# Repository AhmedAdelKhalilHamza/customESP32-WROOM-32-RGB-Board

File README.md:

# custom ESP32 board
custom ESP32 board by Eng/ Ahmed Adel

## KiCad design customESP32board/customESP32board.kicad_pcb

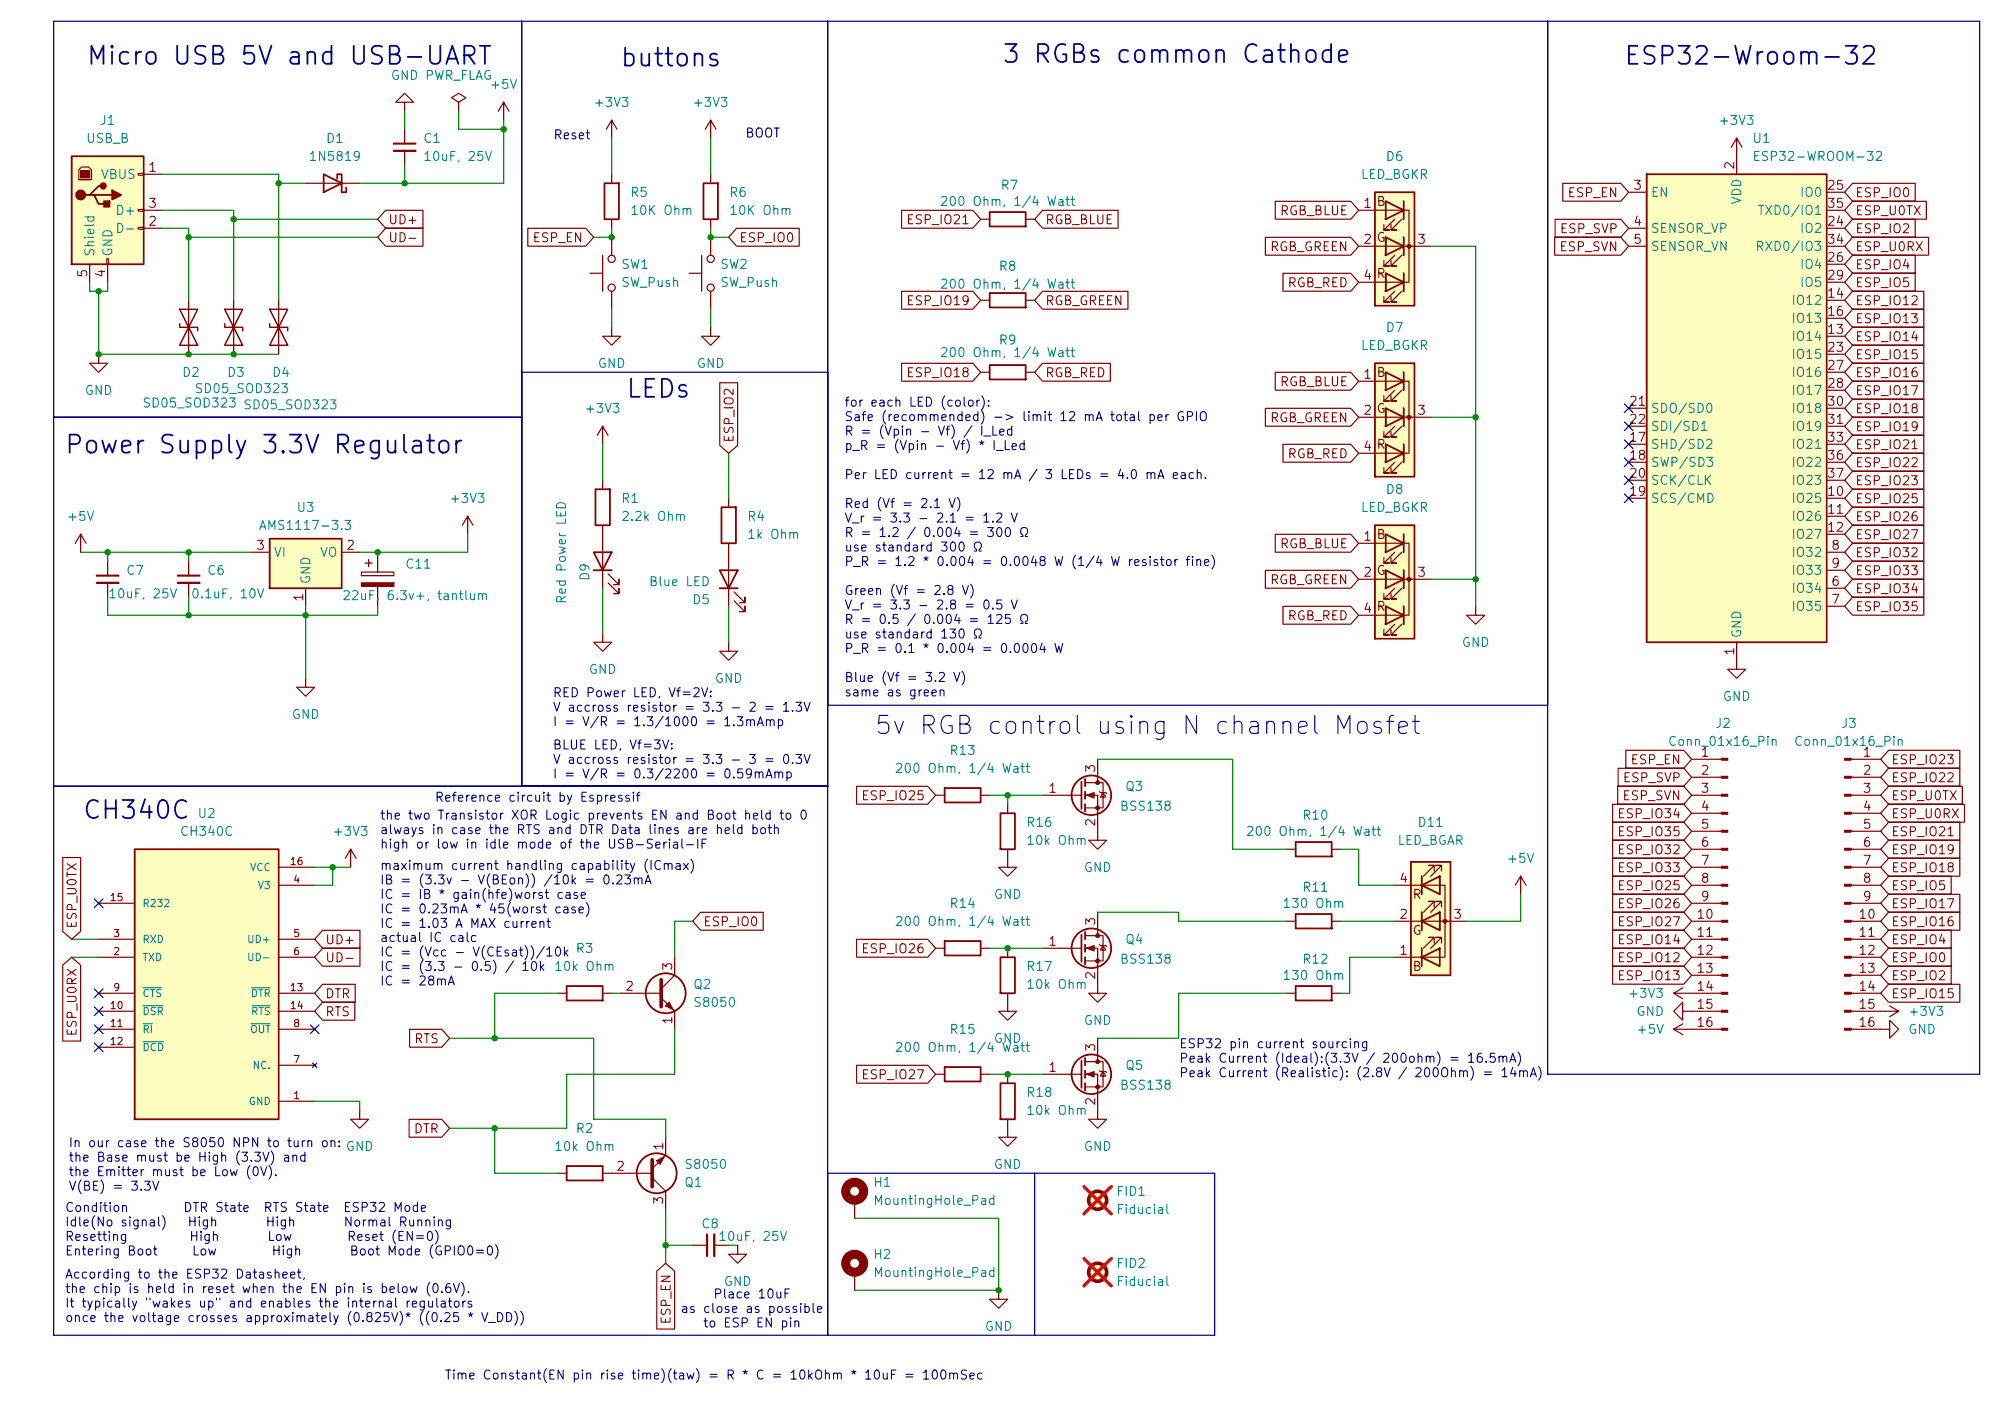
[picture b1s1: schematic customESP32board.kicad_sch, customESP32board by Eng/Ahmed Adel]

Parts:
C1, C7, C8: 10uF, 25V; C_0805_2012Metric
C6: 0.1uF, 10V; C_0603_1608Metric
C11: 22uF, 6.3v+, tantlum; C_1206_3216Metric
D1: 1N5819; D_SMA_Handsoldering
D2, D3, D4: SD05_SOD323; D_SOD-323
D5: Blue LED; LED_0603_1608Metric
D6, D7, D8: LED_BGKR; LED_D5.0mm-4_RGB
D9: Red Power LED; LED_0603_1608Metric
D11: LED_BGAR; LED_D5.0mm-4_RGB
FID1, FID2: Fiducial; Fiducial_0.5mm_Mask1.5mm; not fitted
H1, H2: MountingHole_Pad; MountingHole_2.2mm_M2_Pad_Via
J1: USB_B; USB_B_OST_USB-B1HSxx_Horizontal
J2, J3: Conn_01x16_Pin; PinHeader_1x16_P2.54mm_Vertical
Q1, Q2: S8050; SOT-23
Q3, Q4, Q5: BSS138; SOT-23
R1: 2.2k Ohm; R_0805_2012Metric
R2, R3, R16, R17, R18: 10k Ohm; R_0805_2012Metric
R4: 1k Ohm; R_0603_1608Metric
R5, R6: 10K Ohm; R_1206_3216Metric
R7, R8, R9, R10, R13, R14, R15: 200 Ohm, 1/4 Watt; R_0603_1608Metric
R11, R12: 130 Ohm; R_0805_2012Metric
SW1, SW2: SW_Push; SW_TS-1088-AR02016
U1: ESP32-WROOM-32
U2: CH340C; PARTREV 2G
U3: AMS1117-3.3; SOT-223-3_TabPin2

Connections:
+3V3: C11.1, J2.14, J3.15, R1.2, R5.2, R6.2, U1.2 (VDD), U2.4 (V3), U2.16 (VCC), U3.2 (VO)
+5V: C1.2, C6.1, C7.1, D1.1 (K), D11.3 (A), J2.16, U3.3 (VI)
DTR: Q2.1 (E), R2.1, U2.13 (~DTR)
ESP_EN: C8.1, J2.1, Q1.3 (C), R5.1, SW1.2, U1.3 (EN)
ESP_IO0: J3.12, Q2.3 (C), R6.1, SW2.2, U1.25 (IO0)
ESP_IO2: J3.13, R4.2, U1.24 (IO2)
ESP_IO4: J3.11, U1.26 (IO4)
ESP_IO5: J3.8, U1.29 (IO5)
ESP_IO12: J2.12, U1.14 (IO12)
ESP_IO13: J2.13, U1.16 (IO13)
ESP_IO14: J2.11, U1.13 (IO14)
ESP_IO15: J3.14, U1.23 (IO15)
ESP_IO16: J3.10, U1.27 (IO16)
ESP_IO17: J3.9, U1.28 (IO17)
ESP_IO18: J3.7, R9.1, U1.30 (IO18)
ESP_IO19: J3.6, R8.1, U1.31 (IO19)
ESP_IO21: J3.5, R7.1, U1.33 (IO21)
ESP_IO22: J3.2, U1.36 (IO22)
ESP_IO23: J3.1, U1.37 (IO23)
ESP_IO25: J2.8, R13.2, U1.10 (IO25)
ESP_IO26: J2.9, R14.2, U1.11 (IO26)
ESP_IO27: J2.10, R15.2, U1.12 (IO27)
ESP_IO32: J2.6, U1.8 (IO32)
ESP_IO33: J2.7, U1.9 (IO33)
ESP_IO34: J2.4, U1.6 (IO34)
ESP_IO35: J2.5, U1.7 (IO35)
ESP_SVN: J2.3, U1.5 (SENSOR_VN)
ESP_SVP: J2.2, U1.4 (SENSOR_VP)
ESP_U0RX: J3.4, U1.34 (RXD0/IO3), U2.2 (TXD)
ESP_U0TX: J3.3, U1.35 (TXD0/IO1), U2.3 (RXD)
GND: C1.1, C6.2, C7.2, C8.2, C11.2, D2.1 (A1), D3.1 (A1), D4.1 (A1), D5.1 (K), D6.3 (K), D7.3 (K), D8.3 (K), D9.1 (K), H1.1 (1_1), H2.1 (1_1), J1.4 (GND), J1.5 (Shield), J2.15, J3.16, Q3.2 (S), Q4.2 (S), Q5.2 (S), R16.2, R17.2, R18.2, SW1.1, SW2.1, U1.1 (GND), U1.15 (GND), U1.38 (GND), U1.39 (GND), U2.1 (GND), U3.1 (GND)
unnamed: D1.2 (A), D4.2 (A2), J1.1 (VBUS)
unnamed: D5.2 (A), R4.1
unnamed: D9.2 (A), R1.1
unnamed: D11.1 (BK), R12.2
unnamed: D11.2 (GK), R11.2
unnamed: D11.4 (RK), R10.2
unnamed: Q1.2 (B), R2.2
unnamed: Q2.2 (B), R3.2
unnamed: Q3.3 (D), R10.1
unnamed: Q3.1 (G), R13.1, R16.1
unnamed: Q4.3 (D), R11.1
unnamed: Q4.1 (G), R14.1, R17.1
unnamed: Q5.3 (D), R12.1
unnamed: Q5.1 (G), R15.1, R18.1
RGB_BLUE: D6.1 (BA), D7.1 (BA), D8.1 (BA), R7.2
RGB_GREEN: D6.2 (GA), D7.2 (GA), D8.2 (GA), R8.2
RGB_RED: D6.4 (RA), D7.4 (RA), D8.4 (RA), R9.2
RTS: Q1.1 (E), R3.1, U2.14 (~RTS)
UD+: D3.2 (A2), J1.3 (D+), U2.5 (UD+)
UD-: D2.2 (A2), J1.2 (D-), U2.6 (UD-)

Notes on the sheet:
Condition DTR State RTS State ESP32 Mode Idle(No signal) High High Normal Running Resetting High Low Reset (EN=0) Entering Boot Low High Boot Mode (GPIO0=0)
3 RGBs common Cathode
buttons
BOOT
Power Supply 3.3V Regulator
ESP32 pin current sourcing Peak Current (Ideal):(3.3V / 200ohm) = 16.5mA) Peak Current (Realistic): (2.8V / 200Ohm) = 14mA)
According to the ESP32 Datasheet, the chip is held in reset when the EN pin is below (0.6V). It typically "wakes up" and enables the internal regulators once the voltage crosses approximately (0.825V)* ((0.25 * V_DD))
Reference circuit by Espressif
the two Transistor XOR Logic prevents EN and Boot held to 0 always in case the RTS and DTR Data lines are held both high or low in idle mode of the USB-Serial-IF
LEDs
ESP32-Wroom-32
Reset
Time Constant(EN pin rise time)(taw) = R * C = 10kOhm * 10uF = 100mSec
In our case the S8050 NPN to turn on: the Base must be High (3.3V) and the Emitter must be Low (0V). V(BE) = 3.3V
for each LED (color): Safe (recommended) -> limit 12 mA total per GPIO R = (Vpin - Vf) / I_Led p_R = (Vpin - Vf) * I_Led Per LED current = 12 mA / 3 LEDs = 4.0 mA each. Red (Vf = 2.1 V) V_r = 3.3 − 2.1 = 1.2 V R = 1.2 / 0.004 = 300 Ω use standard 300 Ω P_R = 1.2 * 0.004 = 0.0048 W (1/4 W resistor f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
Place 10uF as close as possible to ESP EN pin
BLUE LED, Vf=3V: V accross resistor = 3.3 - 3 = 0.3V I = V/R = 0.3/2200 = 0.59mAmp
5v RGB control using N channel Mosfet
Micro USB 5V and USB-UART
CH340C
actual IC calc IC = (Vcc - V(CEsat))/10k IC = (3.3 - 0.5) / 10k IC = 28mA
RED Power LED, Vf=2V: V accross resistor = 3.3 - 2 = 1.3V I = V/R = 1.3/1000 = 1.3mAmp
maximum current handling capability (ICmax) IB = (3.3v - V(BEon)) /10k = 0.23mA IC = IB * gain(hfe)worst case IC = 0.23mA * 45(worst case) IC = 1.03 A MAX current

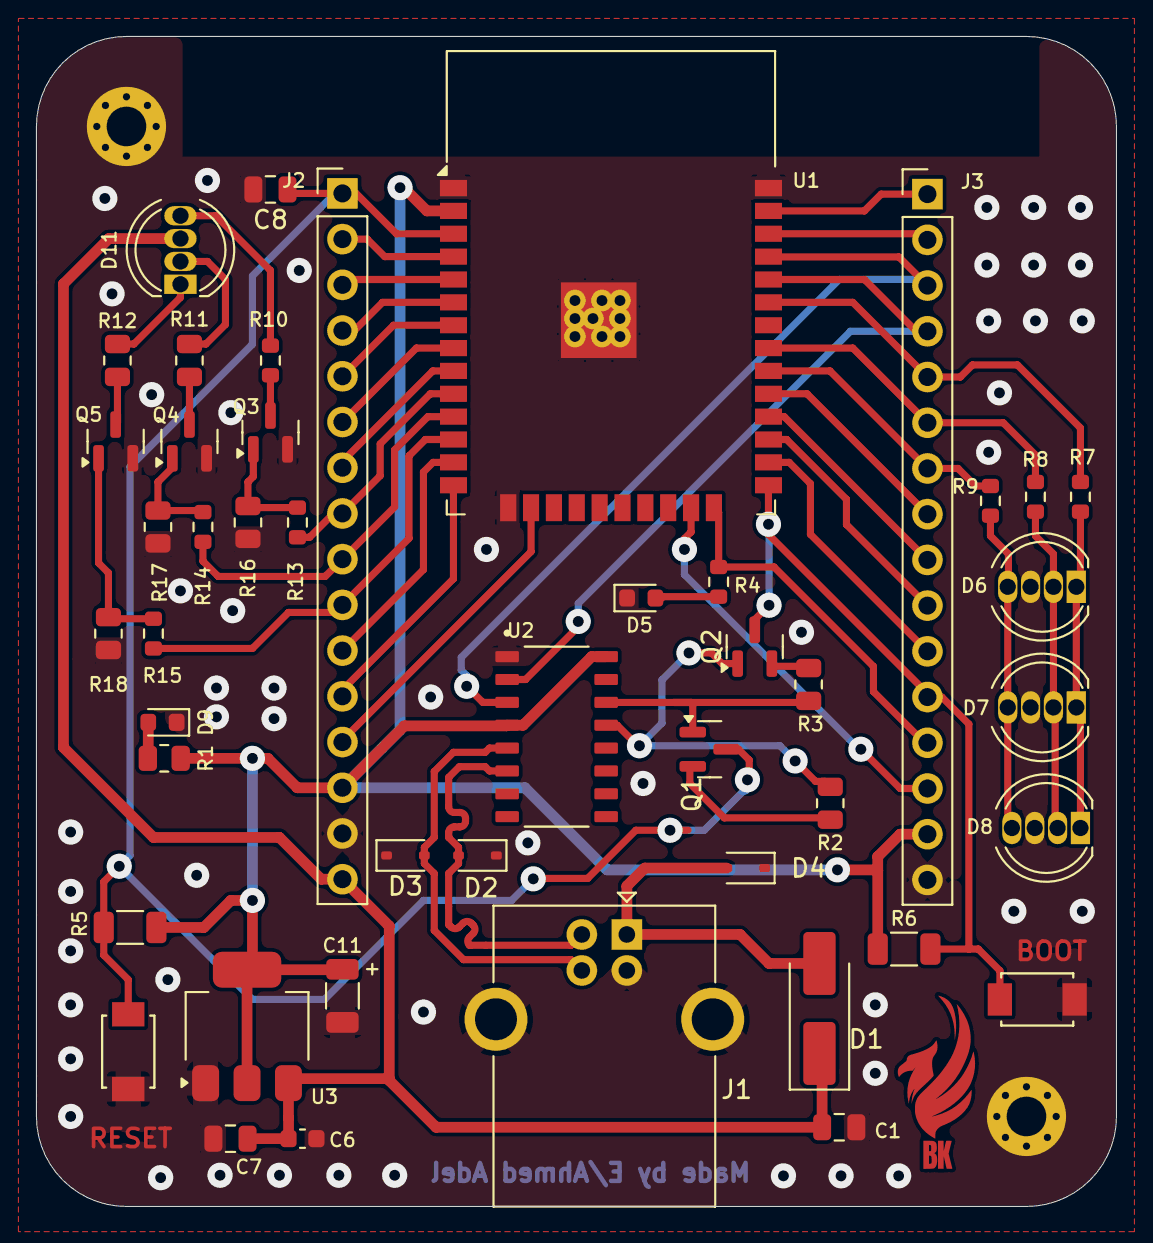
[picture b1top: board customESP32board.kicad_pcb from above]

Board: 2 copper layers, 60.0 x 65.0 mm, 48 parts (0 on the bottom side), 51 nets.

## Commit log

2025-10-11 added pin header text on back silkscreen
2025-10-12 update pcb board size to 65mm x 60mm
2025-10-12 updated D+ and D- routing
2025-10-13 updated connector to USB Type B for production DRC constraints
2025-10-13 updated routing, placemennt, new USB B footprint
2025-10-13 saved files
2025-10-14 updated routing and placement
2025-10-14 finalized board layout V1_1
2025-10-14 generated production files for metanoio
2025-10-17 updated BOM and created price list
2025-10-20 updated components list and updated BOM and calculated price list
2025-10-20 generated BOM again, finished price list and ordered it
2025-10-21 updated resistance 220 Ohm with 0603 footprint to 200 Ohm beacuse its obselete in uge electronics
2025-10-25 updated ibom according do latest bom (sent to production line)
2025-10-29 updated schematic
2025-10-29 updated schematic -> components foot print and BOM
2025-10-30 update layout routing and placement after schematic changes
2026-05-07 updated schematic
    - changed pullup resistors from 10 to 10k
    - updated ch340C bug and updated the capacitor on ESP reset pin (EN pin) to 10uF instead of 0.1uF
2026-05-07 added ESPtool reference
2026-05-07 updated PCB layout placement
2026-05-10 documented esp32 calc of led nmos
2026-05-10 updated PCB layout
2026-05-10 updated routing
